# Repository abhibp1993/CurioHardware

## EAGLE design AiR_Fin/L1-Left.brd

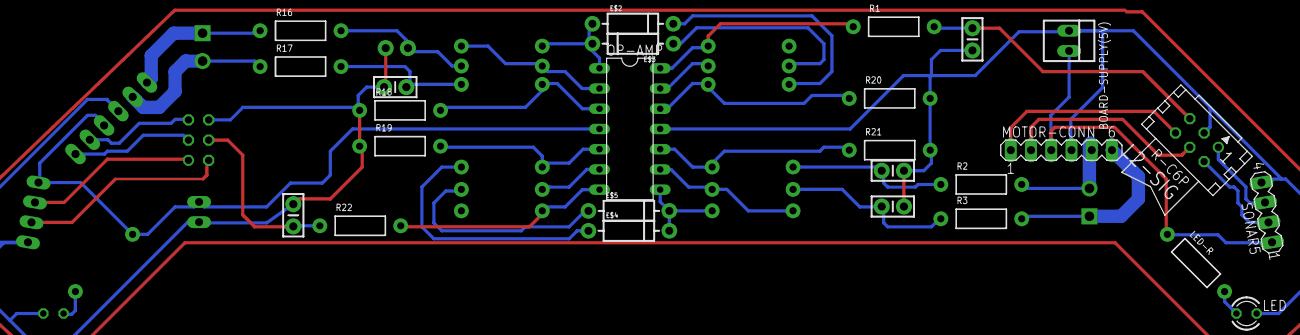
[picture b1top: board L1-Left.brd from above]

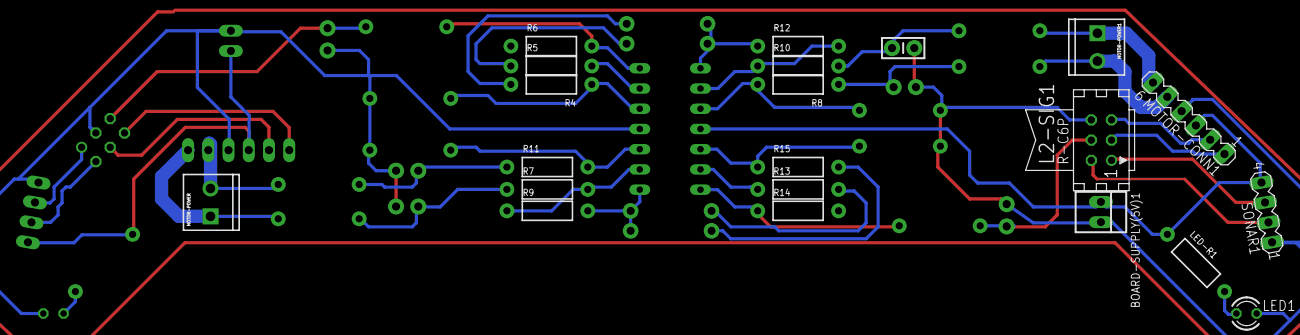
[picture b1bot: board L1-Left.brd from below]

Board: 2 copper layers, 47 parts (21 on the bottom side), 39 nets.

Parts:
BOARD-SUPPLY(5V), BOARD-SUPPLY(5V)1: 22-23-2021
C1, C2, C3, C4, C5, C6: CAP-PTH-SMALL-KIT
E$2, E$3, E$4, E$5: DIODE-1N4001
L2-SIG, L2-SIG1: CON06
LED, LED1: LED3MM
LED-R, LED-R1: AXIAL-0.4
MOTOR-CONN, MOTOR-CONN1: MA06-1
MOTOR-POWER, MOTOR-POWER1: SCREWTERMINAL-3.5MM-2
OP-AMP: DIL14
R1, R2, R3, R4, R5, R6, R7, R8, R9, R10, R11, R12, R13, R14, R15, R16, R17, R18, R19, R20, R21, R22: AXIAL-0.4
SONAR1, SONAR5: MA04-1

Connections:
S$2: E$2.A, E$3.C, OP-AMP.1, R12.P$1
S$3: OP-AMP.2, R10.P$1, R12.P$2
S$4: OP-AMP.3, R8.P$2, R18.P$2
S$5: OP-AMP.5, R15.P$1, R19.P$2
S$6: OP-AMP.6, R13.P$1
S$7: OP-AMP.7, R14.P$1, R22.P$2
S$8: OP-AMP.14, R1.P$1, R6.P$2
S$9: OP-AMP.13, R5.P$2
S$10: OP-AMP.12, R4.P$1, R20.P$1
S$11: OP-AMP.10, R11.P$2, R21.P$1
S$12: OP-AMP.9, R7.P$2, R9.P$1
S$13: E$4.C, E$5.C, OP-AMP.8, R9.P$2
S$14: C2.1, R10.P$2, R16.P$2
S$15: C3.2, R8.P$1, R17.P$2
S$16: E$3.A, R5.P$1
S$17: E$2.C, R4.P$2
S$18: E$4.A, R15.P$2
S$19: E$5.A, R13.P$2
S$20: C4.1, R2.P$1, R11.P$1
S$21: C5.1, R3.P$1, R7.P$1
S$22: MOTOR-CONN1.6, MOTOR-POWER1.1, R16.P$1
S$23: BOARD-SUPPLY(5V).1, C1.1, C4.2, C5.2, L2-SIG.3, LED.K, MOTOR-CONN.4, OP-AMP.11, R20.P$2, R21.P$2, SONAR5.4
S$24: BOARD-SUPPLY(5V)1.2, LED1.K, MOTOR-CONN1.4, SONAR1.1
S$25: MOTOR-CONN1.5, MOTOR-POWER1.2, R17.P$1
S$26: MOTOR-CONN.6, MOTOR-POWER.1, R3.P$2
S$28: C1.2, L2-SIG.5, R1.P$2
S$29: C6.2, L2-SIG1.4, R22.P$1
S$30: BOARD-SUPPLY(5V)1.1, LED-R1.P$1, MOTOR-CONN1.3, OP-AMP.4, SONAR1.4
S$31: L2-SIG1.5, MOTOR-CONN1.2
S$32: L2-SIG1.3, MOTOR-CONN1.1
S$33: LED1.A, LED-R1.P$2
S$34: BOARD-SUPPLY(5V).2, LED-R.P$1, MOTOR-CONN.3, SONAR5.1
S$35: LED.A, LED-R.P$2
S$36: MOTOR-CONN.5, MOTOR-POWER.2, R2.P$2
S$37: L2-SIG.1, SONAR5.3
S$38: L2-SIG.2, SONAR5.2
S$40: L2-SIG.4, MOTOR-CONN.2
S$41: L2-SIG.6, MOTOR-CONN.1
S$45: C2.2, C3.1, C6.1, L2-SIG1.6, R18.P$1, R19.P$1

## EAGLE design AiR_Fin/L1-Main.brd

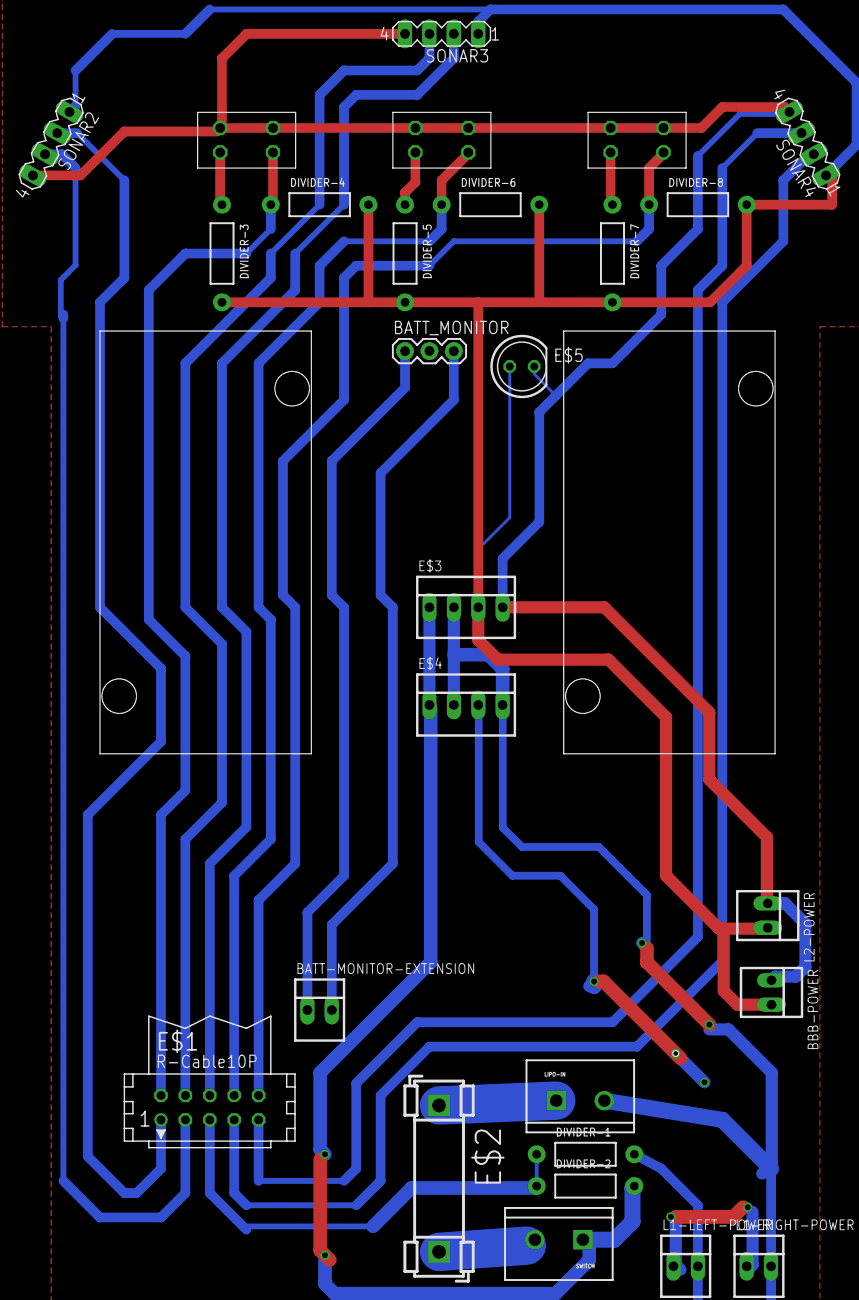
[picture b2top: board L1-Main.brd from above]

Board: 2 copper layers, 29 parts (0 on the bottom side), 23 nets.

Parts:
BATT-MONITOR-EXTENSION: 22-23-2021
BATT_MONITOR: 1X03
BBB-POWER: 22-23-2021
DIVIDER-1, DIVIDER-2, DIVIDER-3, DIVIDER-4, DIVIDER-5, DIVIDER-6, DIVIDER-7, DIVIDER-8: AXIAL-0.4
E$1: CON10
E$2: FUSE_HOLDER_5X20MM
E$3, E$4: 22-23-2041
E$5: LED5MM
L1-LEFT-POWER, L1-RIGHT-POWER, L2-POWER: 22-23-2021
LIPO-IN: SCREWTERMINAL-5MM-2
REG_BBB: 5V3A_REG
REG_EXT: 5V3A_REG
SONAR2, SONAR3, SONAR4: MA04-1
SWITCH: SCREWTERMINAL-5MM-2
TCRT1, TCRT2, TCRT3: TCRT

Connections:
S$2: E$2.1, LIPO-IN.1
S$3: E$2.2, SWITCH.2
S$4: DIVIDER-2.P$2, SWITCH.1
S$5: E$1.3, SONAR2.3
S$6: DIVIDER-1.P$2, L1-LEFT-POWER.2, L1-RIGHT-POWER.2, LIPO-IN.2
S$7: E$1.1, SONAR2.2
S$8: BBB-POWER.1, E$3.4, E$5.K, L2-POWER.1, SONAR3.4, SONAR4.4, TCRT1.1, TCRT1.2, TCRT2.1, TCRT2.2, TCRT3.1, TCRT3.2
S$9: DIVIDER-3.P$1, TCRT1.3
S$10: DIVIDER-5.P$1, TCRT2.3
S$11: DIVIDER-7.P$1, TCRT3.3
S$12: BATT-MONITOR-EXTENSION.1, BATT_MONITOR.1
S$13: DIVIDER-4.P$1, E$1.2, TCRT1.4
S$14: DIVIDER-6.P$1, E$1.8, TCRT2.4
S$15: DIVIDER-8.P$1, E$1.10, TCRT3.4
S$16: BBB-POWER.2, DIVIDER-3.P$2, DIVIDER-4.P$2, DIVIDER-5.P$2, DIVIDER-6.P$2, DIVIDER-7.P$2, DIVIDER-8.P$2, E$3.3, E$5.A, L2-POWER.2, SONAR2.1, SONAR3.1, SONAR4.1
S$17: BATT-MONITOR-EXTENSION.2, BATT_MONITOR.3
S$19: E$1.6, SONAR3.2
S$20: E$1.7, SONAR4.2
S$21: E$1.4, SONAR3.3
S$22: E$1.9, SONAR4.3
S$24: E$3.1, E$4.1
S$25: E$3.2, E$4.2, E$4.4
S$41: DIVIDER-1.P$1, DIVIDER-2.P$1

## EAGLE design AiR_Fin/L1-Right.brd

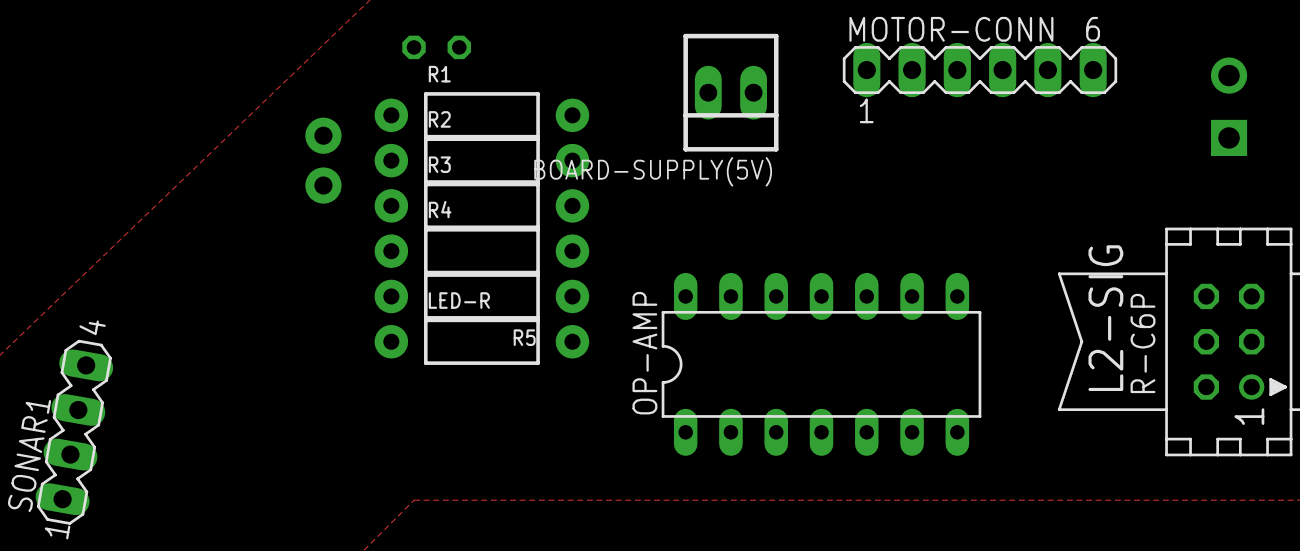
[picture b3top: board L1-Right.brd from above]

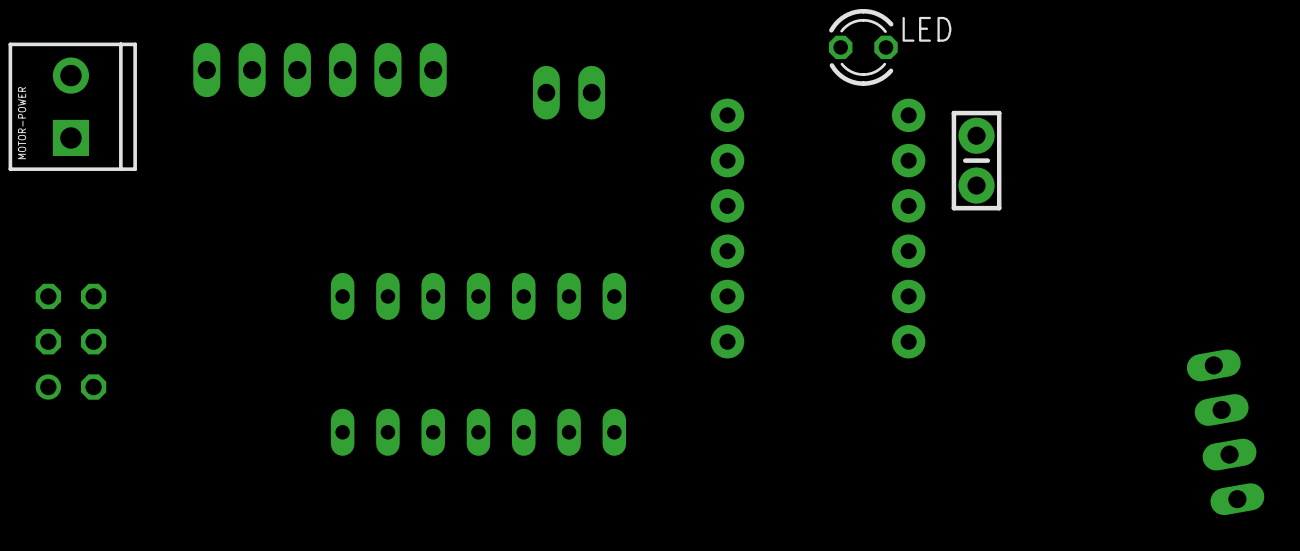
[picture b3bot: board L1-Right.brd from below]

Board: 2 copper layers, 14 parts (3 on the bottom side), 10 nets, no tracks yet.

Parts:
BOARD-SUPPLY(5V): 22-23-2021
C1: CAP-PTH-SMALL-KIT
L2-SIG: CON06
LED: LED3MM
LED-R: AXIAL-0.4
MOTOR-CONN: MA06-1
MOTOR-POWER: SCREWTERMINAL-3.5MM-2
OP-AMP: DIL14
R1, R2, R3, R4, R5: AXIAL-0.4
SONAR1: MA04-1

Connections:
S$1: BOARD-SUPPLY(5V).2, LED.K, OP-AMP.5, OP-AMP.10, OP-AMP.11, SONAR1.1
S$2: BOARD-SUPPLY(5V).1, LED-R.P$2, OP-AMP.4, SONAR1.4
S$3: LED.A, LED-R.P$1
S$5: L2-SIG.3, SONAR1.2
S$6: L2-SIG.5, SONAR1.3
S$7: OP-AMP.1, OP-AMP.2, R5.P$1
S$8: OP-AMP.6, R3.P$1, R5.P$2
S$9: OP-AMP.7, R3.P$2, R4.P$2
S$10: OP-AMP.9, R2.P$2, R4.P$1
S$11: OP-AMP.8, R2.P$1

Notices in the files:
parts and their libraries:
SparkFun-Passives: Licensing: Creative Commons ShareAlike 4.0 International - https://creativecommons.org/licenses/by-sa/4.0
